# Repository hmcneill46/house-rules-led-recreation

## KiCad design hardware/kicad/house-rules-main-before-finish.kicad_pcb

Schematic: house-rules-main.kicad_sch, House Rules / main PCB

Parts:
C1, C3, C5, C7, C11, C12: 100n 50V X7R; C_0603_1608Metric; MPN CC0603KRX7R9BB104; LCSC C14663
C2, C4, C6, C8, C9, C13: 1u 16V X7R; C_0603_1608Metric; MPN 0603B105K160CT; LCSC C108463
C10: 2u2 10V X7R; C_0603_1608Metric; MPN 0603ZC225KAT2A; LCSC C2179699
DS1, DS2, DS3, DS4, DS5, DS6, DS7: LMD07057AUE-101B; MPN LMD07057AUE-101B
F1: 750mA PPTC; Fuse_1206_3216Metric; MPN SMD1206B075TF/16; LCSC C269118
J1: USB CARRIER; JST_SH_BM06B-SRSS-TB_1x06-1MP_P1.00mm_Vertical; MPN BM06B-SRSS-TB(LF)(SN); LCSC C160392
R1, R2, R3, R4, R10, R11, R12, R13: 47k 1%; R_0603_1608Metric; MPN 0603WAF4702T5E; LCSC C25819
R5, R6, R14: 2k2 1%; R_0603_1608Metric; MPN 0603WAF2201T5E; LCSC C4190
R7: 100k 1%; R_0603_1608Metric; MPN 0603WAF1003T5E; LCSC C25803
R8, R9: 10k 1%; R_0603_1608Metric; MPN 0603WAF1002T5E; LCSC C25804
SW1: BOOT; SW_SPST_EVQP7A; MPN EVQP7A01P; LCSC C79167
SW2: RESET; SW_SPST_EVQP7A; MPN EVQP7A01P; LCSC C79167
TP1: GND; TestPoint_Pad_D1.0mm; MPN GND
TP2: 3V3; TestPoint_Pad_D1.0mm; MPN 3V3
TP3: SWDIO; TestPoint_Pad_D1.0mm; MPN SWDIO
TP4: SWCLK; TestPoint_Pad_D1.0mm; MPN SWCLK
TP5: NRST; TestPoint_Pad_D1.0mm; MPN NRST
TP6: 5V; TestPoint_Pad_D1.0mm; MPN 5V
U1, U2, U3, U4: IS31FL3729-QFLS4-TR; QFN-32-1EP_4x4mm_P0.4mm_EP2.65x2.65mm; MPN IS31FL3729-QFLS4-TR; LCSC C2940549
U5: STM32G0B1KBU6; QFN-32-1EP_5x5mm_P0.5mm_EP3.45x3.45mm; MPN STM32G0B1KBU6; LCSC C5159549
U6: TLV75533PDBVR; SOT-23-5; MPN TLV75533PDBVR; LCSC C404027

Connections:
+3V3: C10.1, C11.1, R5.1, R6.1, R8.2, SW1.2, TP2.1, U5.4 (VDD_VDDA), U6.5 (OUT)
+5V: C1.1, C2.1, C3.1, C4.1, C5.1, C6.1, C7.1, C8.1, C9.1, C13.1, F1.2, TP6.1, U1.23 (VCC), U2.23 (VCC), U3.23 (VCC), U4.23 (VCC), U4.28 (AD), U6.1 (IN), U6.3 (EN)
CC1: J1.5, R10.1
CC1_ADC: R10.2, R11.1, U5.7 (PA0_ADC_CC1)
CC2: J1.6, R12.1
CC2_ADC: R12.2, R13.1, U5.8 (PA1_ADC_CC2)
D1_CS1: DS1.12 (ROW1_K), U1.30 (CS1)
D1_CS2: DS1.11 (ROW2_K), U1.31 (CS2)
D1_CS3: DS1.2 (ROW3_K), U1.32 (CS3)
D1_CS4: DS1.9 (ROW4_K), U1.1 (CS4)
D1_CS5: DS1.4 (ROW5_K), U1.2 (CS5)
D1_CS6: DS1.5 (ROW6_K), U1.3 (CS6)
D1_CS7: DS1.6 (ROW7_K), U1.4 (CS7)
D1_CS8: DS2.12 (ROW1_K), U1.5 (CS8)
D1_CS9: DS2.11 (ROW2_K), U1.6 (CS9)
D1_CS10: DS2.2 (ROW3_K), U1.7 (CS10)
D1_CS11: DS2.9 (ROW4_K), U1.8 (CS11)
D1_CS12: DS2.4 (ROW5_K), U1.10 (CS12)
D1_CS13: DS2.5 (ROW6_K), U1.11 (CS13)
D1_CS14: DS2.6 (ROW7_K), U1.12 (CS14)
D1_SW1: DS1.1 (COL1_A), DS2.1 (COL1_A), U1.22 (SW1)
D1_SW2: DS1.3 (COL2_A), DS2.3 (COL2_A), U1.21 (SW2)
D1_SW3: DS1.10 (COL3_A), DS2.10 (COL3_A), U1.20 (SW3)
D1_SW4: DS1.7 (COL4_A), DS2.7 (COL4_A), U1.19 (SW4)
D1_SW5: DS1.8 (COL5_A), DS2.8 (COL5_A), U1.18 (SW5)
D2_CS1: DS3.12 (ROW1_K), U2.30 (CS1)
D2_CS2: DS3.11 (ROW2_K), U2.31 (CS2)
D2_CS3: DS3.2 (ROW3_K), U2.32 (CS3)
D2_CS4: DS3.9 (ROW4_K), U2.1 (CS4)
D2_CS5: DS3.4 (ROW5_K), U2.2 (CS5)
D2_CS6: DS3.5 (ROW6_K), U2.3 (CS6)
D2_CS7: DS3.6 (ROW7_K), U2.4 (CS7)
D2_CS8: DS4.12 (ROW1_K), U2.5 (CS8)
D2_CS9: DS4.11 (ROW2_K), U2.6 (CS9)
D2_CS10: DS4.2 (ROW3_K), U2.7 (CS10)
D2_CS11: DS4.9 (ROW4_K), U2.8 (CS11)
D2_CS12: DS4.4 (ROW5_K), U2.10 (CS12)
D2_CS13: DS4.5 (ROW6_K), U2.11 (CS13)
D2_CS14: DS4.6 (ROW7_K), U2.12 (CS14)
D2_SW1: DS3.1 (COL1_A), DS4.1 (COL1_A), U2.22 (SW1)
D2_SW2: DS3.3 (COL2_A), DS4.3 (COL2_A), U2.21 (SW2)
D2_SW3: DS3.10 (COL3_A), DS4.10 (COL3_A), U2.20 (SW3)
D2_SW4: DS3.7 (COL4_A), DS4.7 (COL4_A), U2.19 (SW4)
D2_SW5: DS3.8 (COL5_A), DS4.8 (COL5_A), U2.18 (SW5)
D3_CS1: DS5.12 (ROW1_K), U3.30 (CS1)
D3_CS2: DS5.11 (ROW2_K), U3.31 (CS2)
D3_CS3: DS5.2 (ROW3_K), U3.32 (CS3)
D3_CS4: DS5.9 (ROW4_K), U3.1 (CS4)
D3_CS5: DS5.4 (ROW5_K), U3.2 (CS5)
D3_CS6: DS5.5 (ROW6_K), U3.3 (CS6)
D3_CS7: DS5.6 (ROW7_K), U3.4 (CS7)
D3_CS8: DS6.12 (ROW1_K), U3.5 (CS8)
D3_CS9: DS6.11 (ROW2_K), U3.6 (CS9)
D3_CS10: DS6.2 (ROW3_K), U3.7 (CS10)
D3_CS11: DS6.9 (ROW4_K), U3.8 (CS11)
D3_CS12: DS6.4 (ROW5_K), U3.10 (CS12)
D3_CS13: DS6.5 (ROW6_K), U3.11 (CS13)
D3_CS14: DS6.6 (ROW7_K), U3.12 (CS14)
D3_SW1: DS5.1 (COL1_A), DS6.1 (COL1_A), U3.22 (SW1)
D3_SW2: DS5.3 (COL2_A), DS6.3 (COL2_A), U3.21 (SW2)
D3_SW3: DS5.10 (COL3_A), DS6.10 (COL3_A), U3.20 (SW3)
D3_SW4: DS5.7 (COL4_A), DS6.7 (COL4_A), U3.19 (SW4)
D3_SW5: DS5.8 (COL5_A), DS6.8 (COL5_A), U3.18 (SW5)
D4_CS1: DS7.12 (ROW1_K), U4.30 (CS1)
D4_CS2: DS7.11 (ROW2_K), U4.31 (CS2)
D4_CS3: DS7.2 (ROW3_K), U4.32 (CS3)
D4_CS4: DS7.9 (ROW4_K), U4.1 (CS4)
D4_CS5: DS7.4 (ROW5_K), U4.2 (CS5)
D4_CS6: DS7.5 (ROW6_K), U4.3 (CS6)
D4_CS7: DS7.6 (ROW7_K), U4.4 (CS7)
D4_SW1: DS7.1 (COL1_A), U4.22 (SW1)
D4_SW2: DS7.3 (COL2_A), U4.21 (SW2)
D4_SW3: DS7.10 (COL3_A), U4.20 (SW3)
D4_SW4: DS7.7 (COL4_A), U4.19 (SW4)
D4_SW5: DS7.8 (COL5_A), U4.18 (SW5)
GND: C1.2, C2.2, C3.2, C4.2, C5.2, C6.2, C7.2, C8.2, C9.2, C10.2, C11.2, C12.2, C13.2, J1.4, J1.MP, R1.2, R2.2, R3.2, R4.2, R7.2, R9.2, R11.2, R13.2, SW2.2, TP1.1, U1.9 (GND), U1.24 (GND), U1.28 (AD), U1.33 (EP_GND), U2.9 (GND), U2.24 (GND), U2.33 (EP_GND), U3.9 (GND), U3.24 (GND), U3.33 (EP_GND), U4.9 (GND), U4.24 (GND), U4.33 (EP_GND), U5.5 (VSS_VSSA), U5.33 (EP_GND), U6.2 (GND)
ISET1: R1.1, U1.25 (ISET)
ISET2: R2.1, U2.25 (ISET)
ISET3: R3.1, U3.25 (ISET)
ISET4: R4.1, U4.25 (ISET)
LED_SDB: R7.1, U1.29 (SDB), U2.29 (SDB), U3.29 (SDB), U4.29 (SDB), U5.15 (PB0_LED_SDB)
NRST: C12.1, R8.1, SW2.1, TP5.1, U5.6 (PF2_NRST)
SCL: R5.2, U1.27 (SCL), U2.27 (SCL), U2.28 (AD), U3.27 (SCL), U4.27 (SCL), U5.30 (PB6_I2C1_SCL)
SDA: R6.2, U1.26 (SDA), U2.26 (SDA), U3.26 (SDA), U3.28 (AD), U4.26 (SDA), U5.31 (PB7_I2C1_SDA)
SWDIO: TP3.1, U5.24 (PA13_SWDIO)
USB_DM: J1.2, U5.22 (PA11_USB_DM)
USB_DP: J1.3, U5.23 (PA12_USB_DP)
VBUS: F1.1, J1.1

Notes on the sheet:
BANK 1 / modules 1 + 2 / address 0x34
BANK 2 / modules 3 + 4 / address 0x35
BANK 3 / modules 5 + 6 / address 0x36
BANK 4 / module 7 / address 0x37
CONTROLLER / USB, artwork and recovery
POWER / protected input and 3V3 regulator
BUS PULL-UPS / shutdown default / CC current-advertisement sensing
SWD RECOVERY / test contacts
Named nets connect all matching labels on this sheet. Every physical package pin is shown; crosses mark intentional no-connects.
47k ISET limits LED pulse current. LED_SDB defaults low. Firmware must authorise USB current before bright playback. USB data and recovery share the carrier harness.

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
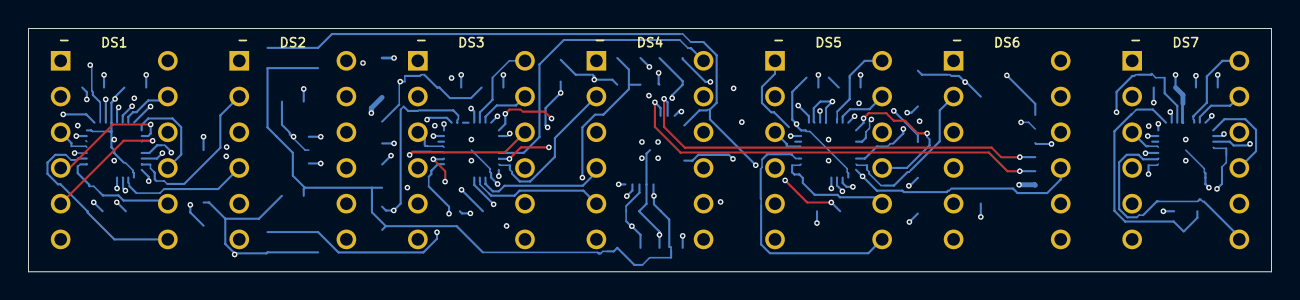
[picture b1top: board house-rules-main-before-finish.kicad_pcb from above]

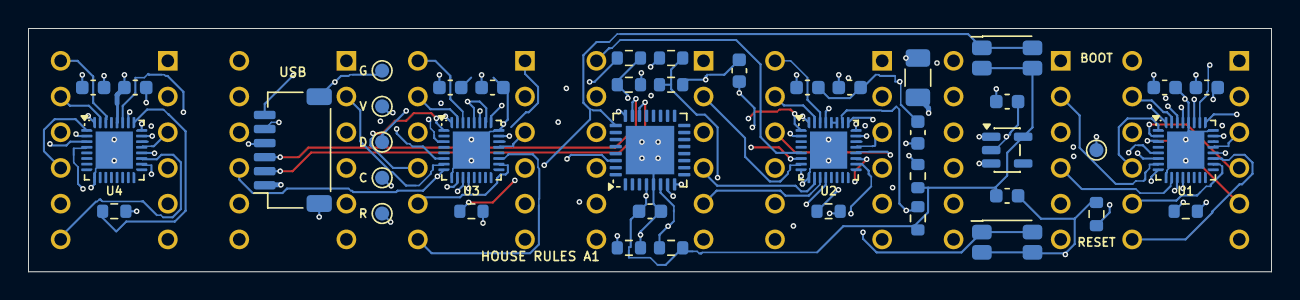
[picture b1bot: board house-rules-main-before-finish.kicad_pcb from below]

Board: 6 copper layers, 88.4 x 17.3 mm, 49 parts (42 on the bottom side), 89 nets.

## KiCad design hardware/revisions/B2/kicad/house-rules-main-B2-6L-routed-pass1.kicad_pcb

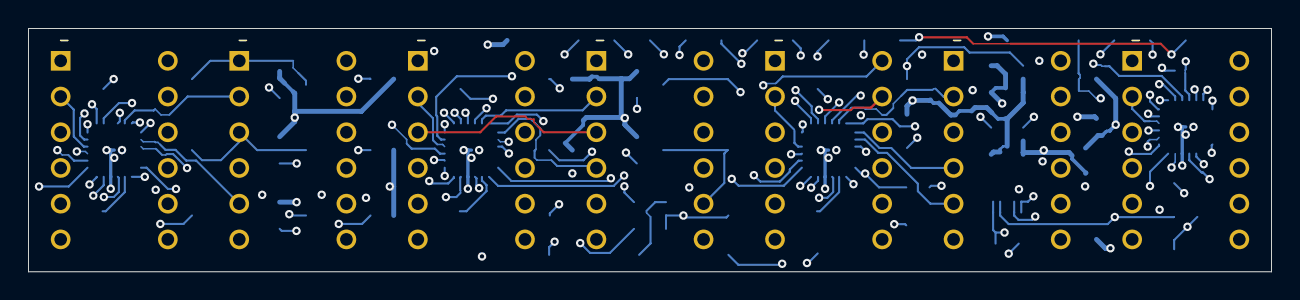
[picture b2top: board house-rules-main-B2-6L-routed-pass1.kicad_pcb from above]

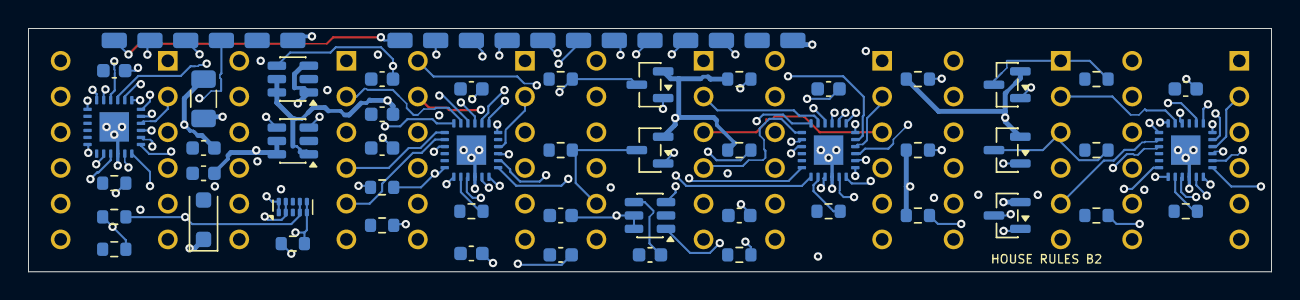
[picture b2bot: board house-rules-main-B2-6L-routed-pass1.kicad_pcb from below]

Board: 6 copper layers, 88.4 x 17.3 mm, 74 parts (67 on the bottom side), 87 nets.

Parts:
C1, C2, C3, C4: 100n 50V X7R; C_0603_1608Metric
C5, C6, C7, C14: 1u 16V X7R; C_0603_1608Metric
C8: 4u7 16V X5R; C_0603_1608Metric
C9, C10, C13: 1n 50V X7R; C_0603_1608Metric
C11, C12: 10n 50V X7R; C_0603_1608Metric
D1: SMF5.0A; D_SOD-123F
DS1, DS2, DS3, DS4, DS5, DS6, DS7: LMD07057AUE-101B
F1: 750mA PPTC; Fuse_1206_3216Metric
J1: +5V; WirePad_B2
J2, J14: GND; WirePad_B2
J3: +3V3; WirePad_B2
J4: SIN; WirePad_B2
J5: SCLK; WirePad_B2
J6: LAT; WirePad_B2
J7: BLANK; WirePad_B2
J8: DRIVER_EN; WirePad_B2
J9: CC1_ADC; WirePad_B2
J10: CC2_ADC; WirePad_B2
J11, J17: USB_DM; WirePad_B2
J12, J18: USB_DP; WirePad_B2
J13: VBUS; WirePad_B2
J15: CC1; WirePad_B2
J16: CC2; WirePad_B2
Q1, Q2, Q3, Q4, Q5: AO3401A; SOT-23
R1, R2, R3, R4: 6k98 1%; R_0603_1608Metric
R5, R6, R7, R8, R9, R15: 4k7 1%; R_0603_1608Metric
R10, R11, R12, R13, R14: 10k 1%; R_0603_1608Metric
R16: 100k 1%; R_0603_1608Metric
R17, R18, R19, R20: 47k 1%; R_0603_1608Metric
U1, U2, U3, U4: TLC59282RGER; RGE0024C
U5, U6, U8: TPS22918DBVR; SOT-23-6
U7: TPD4E05U06DQAR; USON-10_2.5x1.0mm_P0.5mm

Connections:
+3V3: C5.1, J3.1, U5.1
+5V: C6.1, J1.1, U6.1, U8.5, U8.6
BLANK: J7.1, R15.1, U1.18, U2.18, U3.18, U4.18
CC1: J15.1, R17.1, U7.4, U7.7
CC1_ADC: C11.1, J9.1, R17.2, R18.1
CC2: J16.1, R19.1, U7.5, U7.6
CC2_ADC: C12.1, J10.1, R19.2, R20.1
COL1_A: DS1.1, DS2.1, DS3.1, DS4.1, DS5.1, DS6.1, DS7.1, Q1.3, R10.1
COL1_GATE: Q1.1, R5.1, U4.9
COL2_A: DS1.3, DS2.3, DS3.3, DS4.3, DS5.3, DS6.3, DS7.3, Q2.3, R11.1
COL2_GATE: Q2.1, R6.1, U4.10
COL3_A: DS1.10, DS2.10, DS3.10, DS4.10, DS5.10, DS6.10, DS7.10, Q3.3, R12.1
COL3_GATE: Q3.1, R7.1, U4.11
COL4_A: DS1.7, DS2.7, DS3.7, DS4.7, DS5.7, DS6.7, DS7.7, Q4.3, R13.1
COL4_GATE: Q4.1, R8.1, U4.12
COL5_A: DS1.8, DS2.8, DS3.8, DS4.8, DS5.8, DS6.8, DS7.8, Q5.3, R14.1
COL5_GATE: Q5.1, R9.1, U4.13
CT_3V3: C9.1, U5.4
CT_5V: C10.1, U6.4
CT_INPUT: C13.1, U8.4
D1_ROW1_K: DS1.12, U1.2
D1_ROW2_K: DS1.11, U1.3
D1_ROW3_K: DS1.2, U1.4
D1_ROW4_K: DS1.9, U1.5
D1_ROW5_K: DS1.4, U1.6
D1_ROW6_K: DS1.5, U1.7
D1_ROW7_K: DS1.6, U1.8
D1_ROW8_K: DS2.12, U1.9
D1_ROW9_K: DS2.11, U1.10
D1_ROW10_K: DS2.2, U1.11
D1_ROW11_K: DS2.9, U1.12
D1_ROW12_K: DS2.4, U1.13
D1_ROW13_K: DS2.5, U1.14
D1_ROW14_K: DS2.6, U1.15
D2_ROW1_K: DS3.12, U2.2
D2_ROW2_K: DS3.11, U2.3
D2_ROW3_K: DS3.2, U2.4
D2_ROW4_K: DS3.9, U2.5
D2_ROW5_K: DS3.4, U2.6
D2_ROW6_K: DS3.5, U2.7
D2_ROW7_K: DS3.6, U2.8
D2_ROW8_K: DS4.12, U2.9
D2_ROW9_K: DS4.11, U2.10
D2_ROW10_K: DS4.2, U2.11
D2_ROW11_K: DS4.9, U2.12
D2_ROW12_K: DS4.4, U2.13
D2_ROW13_K: DS4.5, U2.14
D2_ROW14_K: DS4.6, U2.15
D3_ROW1_K: DS5.12, U3.2
D3_ROW2_K: DS5.11, U3.3
D3_ROW3_K: DS5.2, U3.4
D3_ROW4_K: DS5.9, U3.5
D3_ROW5_K: DS5.4, U3.6
D3_ROW6_K: DS5.5, U3.7
D3_ROW7_K: DS5.6, U3.8
D3_ROW8_K: DS6.12, U3.9
D3_ROW9_K: DS6.11, U3.10
D3_ROW10_K: DS6.2, U3.11
D3_ROW11_K: DS6.9, U3.12
D3_ROW12_K: DS6.4, U3.13
D3_ROW13_K: DS6.5, U3.14
D3_ROW14_K: DS6.6, U3.15
D4_ROW1_K: DS7.12, U4.2
D4_ROW2_K: DS7.11, U4.3
D4_ROW3_K: DS7.2, U4.4
D4_ROW4_K: DS7.9, U4.5
D4_ROW5_K: DS7.4, U4.6
D4_ROW6_K: DS7.5, U4.7
D4_ROW7_K: DS7.6, U4.8
DRIVER_EN: J8.1, R16.1, U5.3, U6.3
FUSED_VBUS: C14.1, F1.2, U8.1, U8.3
GND: C1.2, C2.2, C3.2, C4.2, C5.2, C6.2, C7.2, C8.2, C9.2, C10.2, C11.2, C12.2, C13.2, C14.2, D1.2, J2.1, J14.1, R1.2, R2.2, R3.2, R4.2, R10.2, R11.2, R12.2, R13.2, R14.2, R16.2, R18.2, R20.2, U1.22, U1.25, U2.22, U2.25, U3.22, U3.25, U4.22, U4.25, U5.2, U6.2, U7.3, U7.8, U8.2
IREF1: R1.1, U1.20
IREF2: R2.1, U2.20
IREF3: R3.1, U3.20
IREF4: R4.1, U4.20
LAT: J6.1, U1.1, U2.1, U3.1, U4.1
SCLK: J5.1, U1.24, U2.24, U3.24, U4.24
SERIAL_1_2: U1.19, U2.23
SERIAL_2_3: U2.19, U3.23
SERIAL_3_4: U3.19, U4.23
SIN: J4.1, U1.23
SW_3V3: C1.1, C2.1, C3.1, C4.1, C7.1, R15.2, U1.21, U2.21, U3.21, U4.21, U5.5, U5.6
USB_DM: J11.1, J17.1, U7.1, U7.10
USB_DP: J12.1, J18.1, U7.2, U7.9
VBUS: D1.1, F1.1, J13.1
VLED_5V: C8.1, Q1.2, Q2.2, Q3.2, Q4.2, Q5.2, R5.2, R6.2, R7.2, R8.2, R9.2, U6.5, U6.6
